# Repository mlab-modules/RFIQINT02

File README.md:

# RFIQINT02B -  RF signal I/Q interface

## Parameters

| Parameter | Value | Description |
|-----------|-------|-------------|
| Frequency range | 100 - 1000 MHz |  |
| Interface | RJ45 | CAT 7/A cable is expected |
| Operating and storage temperature | -20 - +30°C |  |
| Operational input voltage for Antenna | 9 - 12 V |  |
| Operational input voltage  | 3.3-3.6 V | 130 mA for LO buffer core |

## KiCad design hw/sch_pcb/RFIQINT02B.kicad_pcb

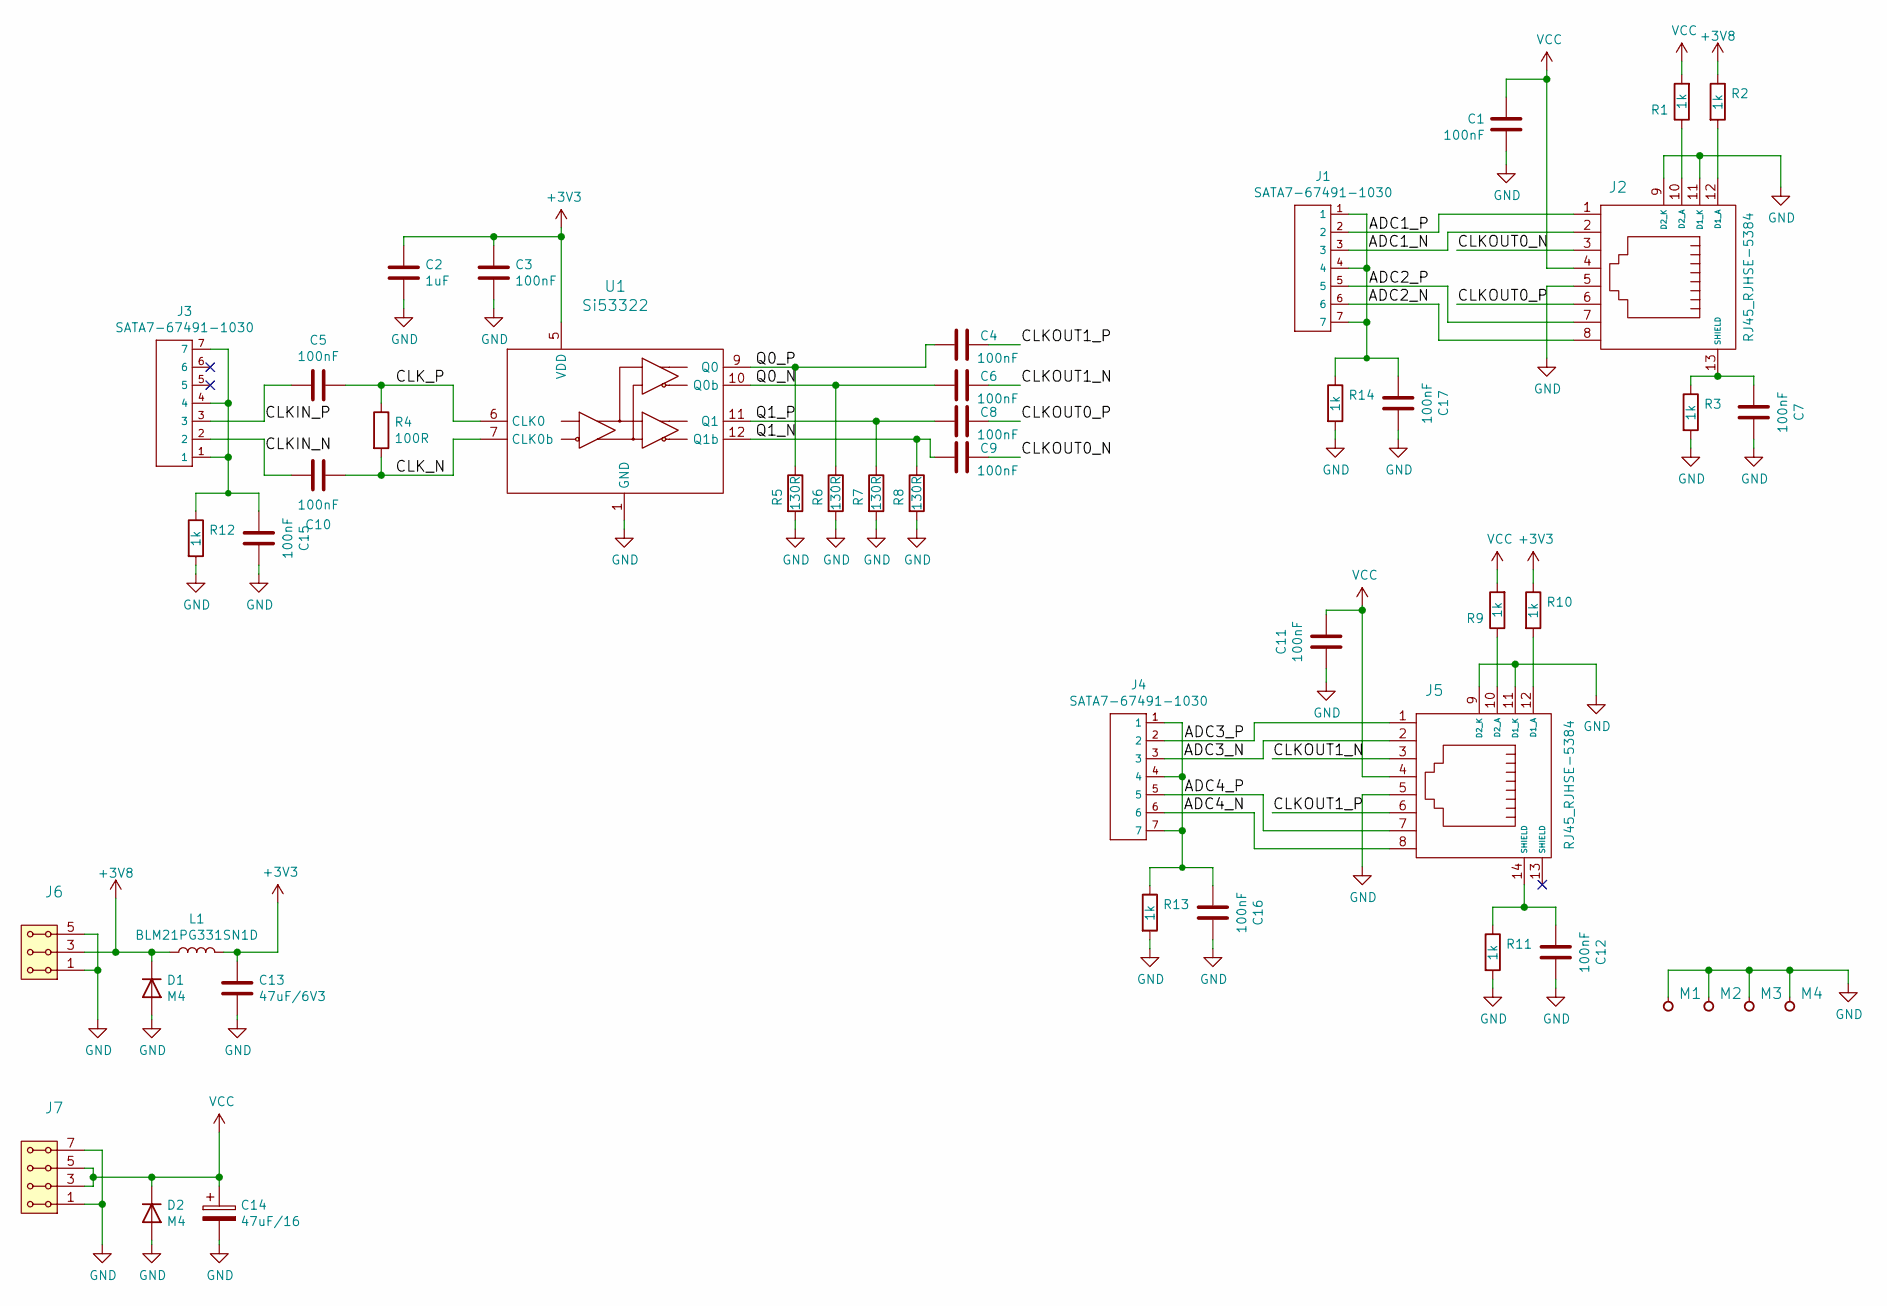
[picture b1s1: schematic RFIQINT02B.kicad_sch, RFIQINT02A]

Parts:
C1, C3, C4, C5, C6, C7, C8, C9, C10, C11, C12, C15, C16, C17: 100nF; R_0805_2012Metric
C2: 1uF; C_0805_2012Metric
C13: 47uF/6V3; C_0805_2012Metric
C14: 47uF/16; CP_EIA-7132-28_AVX-C
D1, D2: M4; D_SMA
J1, J3, J4: SATA7-67491-1030; SATA-7_THT_VERT_2
J2, J5: RJ45_RJHSE-5384; RJHSE-5384(RJ45)
J6: HEADER_2x03_PARALLEL; Straight_2x03
J7: HEADER_2x04_PARALLEL; Straight_2x04
L1: BLM21PG331SN1D; R_0805_2012Metric
M1, M2, M3, M4: HOLE; MountingHole_3mm
R1, R2, R3, R9, R10, R11, R12, R13, R14: 1k; R_0805_2012Metric
R4: 100R; R_0805_2012Metric
R5, R6, R7, R8: 130R; R_0805_2012Metric
U1: Si53322; QFN-16-1EP_3x3mm_P0.5mm_EP1.7x1.7mm_ThermalVias

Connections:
+3V3: C2.1, C3.1, C13.1, L1.2, R10.1, U1.5 (VDD)
+3V8: D1.1 (K), J6.3, J6.4, L1.1, R2.1
/ADC1_N: J1.3, J2.2
/ADC1_P: J1.2, J2.1
/ADC2_N: J1.6, J2.8
/ADC2_P: J1.5, J2.7
/ADC3_N: J4.3, J5.2
/ADC3_P: J4.2, J5.1
/ADC4_N: J4.6, J5.8
/ADC4_P: J4.5, J5.7
/CLKIN_N: C10.1, J3.2
/CLKIN_P: C5.1, J3.3
/CLKOUT0_N: C9.2, J2.3
/CLKOUT0_P: C8.2, J2.6
/CLKOUT1_N: C6.2, J5.3
/CLKOUT1_P: C4.2, J5.6
/CLK_N: C10.2, R4.2, U1.7 (CLK0b)
/CLK_P: C5.2, R4.1, U1.6 (CLK0)
/Q0_N: C6.1, R6.1, U1.10 (Q0b)
/Q0_P: C4.1, R5.1, U1.9 (Q0)
/Q1_N: C9.1, R8.1, U1.12 (Q1b)
/Q1_P: C8.1, R7.1, U1.11 (Q1)
GND: C1.1, C2.2, C3.2, C7.2, C11.1, C12.2, C13.2, C14.2, C15.2, C16.2, C17.2, D1.2 (A), D2.2 (A), J2.5, J2.9 (D2_K), J2.11 (D1_K), J5.5, J5.9 (D2_K), J5.11 (D1_K), J6.1, J6.2, J6.5, J6.6, J7.1, J7.2, J7.7, J7.8, M1.1, M2.1, M3.1, M4.1, R3.2, R5.2, R6.2, R7.2, R8.2, R11.2, R12.2, R13.2, R14.2, U1.1 (GND), U1.17 (GND)
unnamed: C7.1, J2.13 (SHIELD), R3.1
unnamed: C12.1, J5.14 (SHIELD), R11.1
unnamed: C17.1, J1.1, J1.4, J1.7, R14.1
unnamed: J2.10 (D2_A), R1.1
unnamed: J2.12 (D1_A), R2.2
unnamed: C15.1, J3.1, J3.4, J3.7, R12.1
unnamed: C16.1, J4.1, J4.4, J4.7, R13.1
unnamed: J5.10 (D2_A), R9.1
unnamed: J5.12 (D1_A), R10.2
VCC: C1.2, C11.2, C14.1, D2.1 (K), J2.4, J5.4, J7.3, J7.4, J7.5, J7.6, R1.2, R9.2

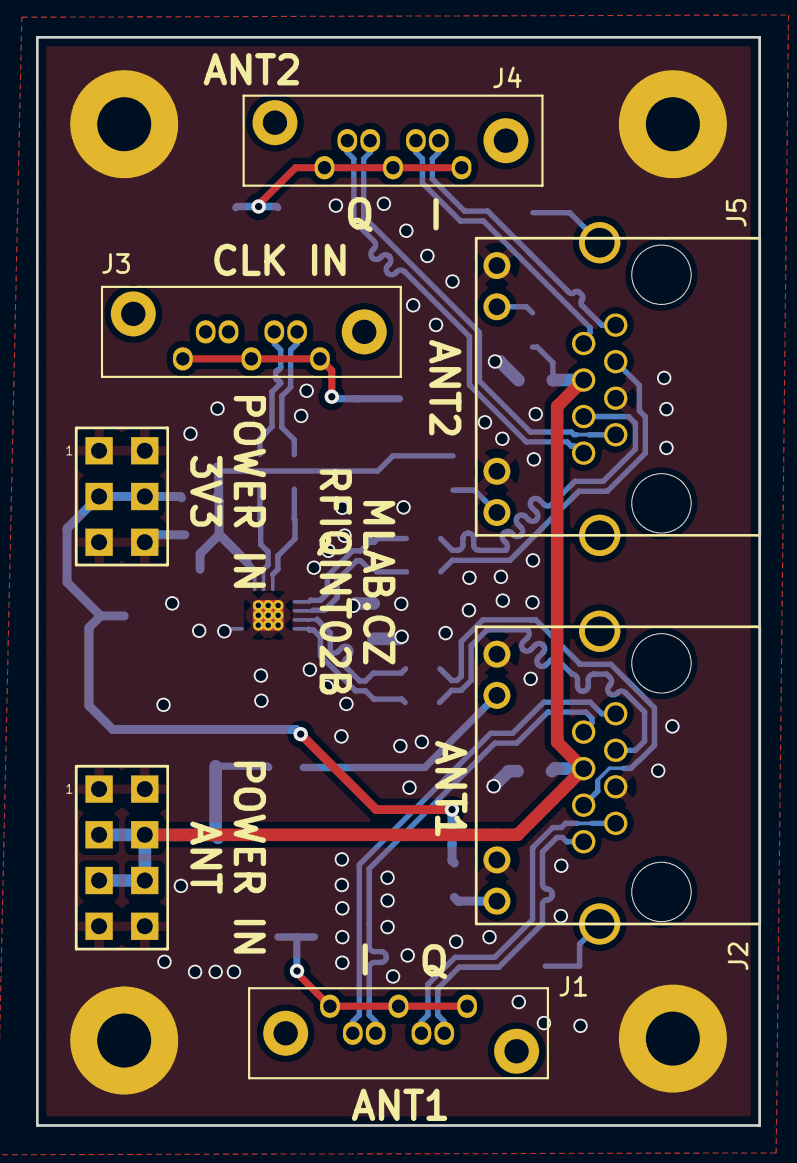
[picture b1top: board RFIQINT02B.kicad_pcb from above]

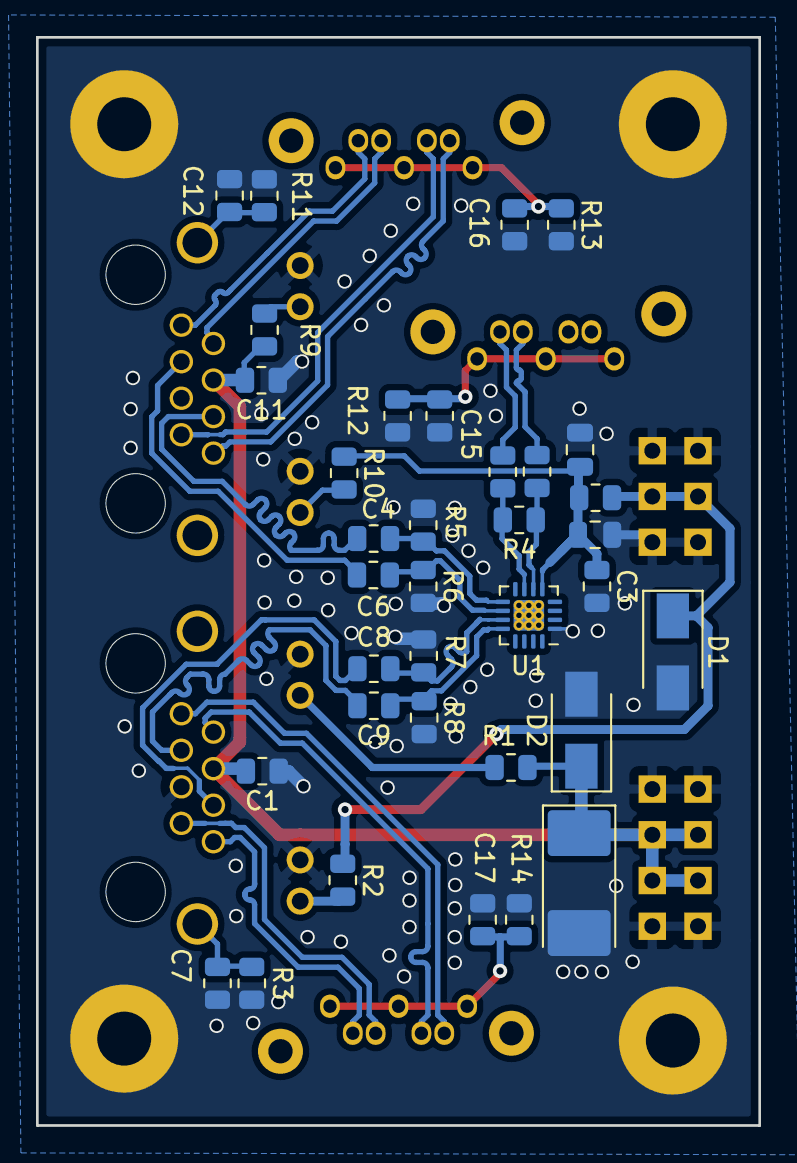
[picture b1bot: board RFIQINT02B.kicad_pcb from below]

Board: 2 copper layers, 40.1 x 60.5 mm, 46 parts (37 on the bottom side), 33 nets.

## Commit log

2020-08-10 Tvorba schema a PCB
2020-08-10 Odebrani slozky pro HDL nebot u tohoto modulu HDL kod snad nebude nikdy potreba.
2020-09-21 Edit PCB
2020-11-01 Cleanup and layer visibility change.
2020-11-02 Test of differential pair skew tune.
2021-04-14 Improve documentation. Generate new image. Remove irrelavant symbols in silkscreen.
2021-06-17 Edit UST ID
2021-06-18 Update project and title block.
2021-06-18 remove vias from differential pairs routing.
2021-06-18 Update net classes.
2021-06-18 Apply net class parameters.
2021-06-21 Tune skew of differential pairs.
    Use the RJ45 connector's LED as power indicators.
2021-06-22 Add grounding vias remove thermal relief at U1 grounding. #3.
2021-06-23 Generating production data
2021-06-30 Edit B.FAB
2021-07-01 New bom
2022-03-08 Update to KiCAD version 6.0.
2022-03-11 Adding datasheet.
2022-05-13 Renaming KiCad projekt
2022-05-13 #6 #5
2022-05-13 Adding actions and pictures
2022-05-13 Update actions products
2022-05-25 Editace podkladů po osazení
2023-05-25 automated commit; add github actions
2023-05-25 Update metadata files
2023-05-28 Update workflow files
2023-07-05 automated commit; rename source files to new naming convence
2023-09-16 Update image to image_title
2023-09-16 Update status
2024-07-03 Crop out black border.
